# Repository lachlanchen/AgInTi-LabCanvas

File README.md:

[English](README.md) · [العربية](i18n/README.ar.md) · [Español](i18n/README.es.md) · [Français](i18n/README.fr.md) · [日本語](i18n/README.ja.md) · [한국어](i18n/README.ko.md) · [Tiếng Việt](i18n/README.vi.md) · [中文 (简体)](i18n/README.zh-Hans.md) · [中文（繁體）](i18n/README.zh-Hant.md) · [Deutsch](i18n/README.de.md) · [Русский](i18n/README.ru.md)

<p align="center">

</p>

<h1 align="center">AgInTi LabCanvas</h1>

<p align="center">
  <strong>Editable scientific figure and experiment-design studio for agent workflows.</strong><br>
  Chat, preview, decompose, route, and rebuild paper figures through Blender, OpenSCAD, BioRender, AgInTi, KiCad, Unity, Unreal, and MCP-style tool bridges.
</p>

<!-- support:start -->

<!-- support:end -->

## What It Does

AgInTi LabCanvas is a small local control plane for agent-assisted scientific visuals and app automation. It keeps generated figures editable: an overview image can start an idea, but final outputs are rebuilt from atomic parts, scene specs, CAD files, manifests, and tool-specific artifacts.

## Current Highlights

| Area | What is ready | Entry point |
| --- | --- | --- |
| Workspace agent | Persistent direct chat, dynamic low-to-xhigh model routing, durable tasks, cancellation, and artifact return across all lab tools | [docs/WORKSPACE_AGENT.md](docs/WORKSPACE_AGENT.md) |
| Web studio | Agent chat, room-based persistent sessions, artifact canvas, backend settings, multilingual UI | `labcanvas web --port 8787 --open`, `/rooms` |
| Presentations | Editable manifest-driven PPTX, selective visual assets, generated-image policy gates, and PDF/PNG preview inspection | `labcanvas presentation`, [pipeline](docs/PRESENTATION_PIPELINE.md) |
| Paper figures | Exact `NxM` SVG grids, AgInTi image dry-run payloads, editable artifact manifest | [docs/EDITABLE_FIGURE_PIPELINE.md](docs/EDITABLE_FIGURE_PIPELINE.md) |
| Grant projects | Durable Codex goal workspace, traceable evidence, editable BioRender/SVG/TeX figures, checked LaTeX/PDF, and mandatory chat delivery | `labcanvas grant init`, `labcanvas grant run`, [BioRender bridge](agentic_tools/biorender_agent/README.md) |
| Protein structures | Reused ProteinStructure AlphaFold Server pipeline, persistent logged-in CDP/noVNC browser, downloads, metrics, plots, and screenshots | `labcanvas protein start`, [handoff](references/proteinstructure-alphafold-labcanvas-handoff.md) |
| 3D setup renders | JSON scene specs to Blender PNG and `.blend` output | [docs/SCENE_SPEC.md](docs/SCENE_SPEC.md) |
| CAD devices | OpenSCAD exports and C-mount reflector adapter CAD | [cad/README.md](cad/README.md) |
| Board/CAD tasks | Shared CLI and web-chat workflow for KiCad, OpenSCAD, renders, and manufacturing prep | [docs/BOARD_CAD_TASKS.md](docs/BOARD_CAD_TASKS.md) |
| PCB manufacturing | KiCad HYBEC and Lumileds boards, DRC/ERC, JLCPCB Gerber ZIPs | [pcb](pcb) |
| LabVIEW automation | Linux install probe, MCP candidate research, stdio-to-HTTP bridge | [agentic_tools/labview_mcp_agent](agentic_tools/labview_mcp_agent) |
| Android control | Dedicated noVNC/scrcpy desktop and ADB wrapper for the Mi MIX 2S real device plus matching AVD profile | [docs/ANDROID_DEVICE_CONTROL.md](docs/ANDROID_DEVICE_CONTROL.md) |
| WeChat chatops | Isolated Linux GUI, direct local message mirror, exact-token per-chat media isolation, save-only default for unaccompanied videos, serialized text/file delivery, bounded no-backlog recovery, and CAD/PCB/Blender artifact return | [docs/WECHAT_AUTOMATION.md](docs/WECHAT_AUTOMATION.md), [full control manual](agentic_tools/wechat_gui_agent/docs/FULL_CONTROL_MANUAL.md), [robust operations](agentic_tools/wechat_gui_agent/docs/ROBUST_EFFICIENT_OPERATIONS.md) |
| WeCom bridge | Official AI Bot and `wecom-cli` transports plus allowlisted GUI/Android relays, exact voice/media transcription, content-idempotent file sends, per-chat sessions, member archives, immediate `#daily` research, and LaTeX report recovery | [setup and architecture](docs/WECOM_API_BRIDGE.md), [stable GUI interface](agentic_tools/wecom_agent/docs/GUI_RELAY_INTERFACE.md) |
| LALACHAN video handoff | Story drafting, Xiaoyunque browser generation, MP4 download, repo/Nutstore copy, and LazyEdit permission gates for WeChat workers | [references/lalachan-story-video-handoff-for-wechat.md](references/lalachan-story-video-handoff-for-wechat.md) |
| Video publish handoff | Agents resolve exact videos and context, then delegate subtitle correction, metadata, logo/subtitle burn, packaging, and public posting to LazyEdit/AutoPublish | [references/lazyedit-agent-integration-handoff.md](references/lazyedit-agent-integration-handoff.md) |
| Social content agent | Persistent Codex campaigns, source-grounded platform drafts, SQLite history, Postiz/X MCP adapters, and exact-content publication approvals | [agentic_tools/social_content_agent](agentic_tools/social_content_agent) |
| App routing | Blender, BioRender, Unity, Unreal, and custom target dispatch | [docs/RESEARCH.md](docs/RESEARCH.md) |

## Quick Start

### Model Policy

Automatic LabCanvas turns use the shared [`configs/model-policy.json`](configs/model-policy.json):
AgInTiFlow is the primary persistent backend, with DeepSeek first and LocalLLM
as a same-session provider handoff. Established LabCanvas and sibling-project
routines remain the execution layer. Codex (`auto-code-review` or
`gpt-5.6-sol`) and Claude Code remain explicit opt-in compatibility backends;
explicit backend, model, and effort selections still win. See the
[AgInTi primary-agent handoff](references/aginti-primary-labcanvas-agent-handoff-2026-08-18.md)
for goal, context, artifact, fallback, and acceptance contracts.

Run from a source checkout:

```bash
PYTHONPATH=src python -m agenticapp list
PYTHONPATH=src python -m agenticapp doctor
PYTHONPATH=src python -m agenticapp web --port 8787 --open
PYTHONPATH=src python -m agenticapp agent capabilities
PYTHONPATH=src python -m agenticapp agent chat "Design and render a C-mount sensor holder"
PYTHONPATH=src python -m agenticapp grant run "Draft specific aims with verified evidence and an editable figure" --title "Research Grant" --dry-run
PYTHONPATH=src python -m agenticapp studio biorender-figure "Three-panel mechanism figure" --panel "A: mechanism" --panel "B: intervention" --panel "C: validation" --json
PYTHONPATH=src python -m agenticapp protein start --json
PYTHONPATH=src python -m agenticapp protein status --json
PYTHONPATH=src python -m agenticapp protein submit references/target.fasta --dry-run
PYTHONPATH=src python -m agenticapp studio figure-grid "optical device icons 2x3" --rows 2 --cols 3
PYTHONPATH=src python -m agenticapp studio lab-task "prepare Lumileds no-resistor PCB and C-mount reflector CAD"
PYTHONPATH=src python -m agenticapp wechat worker reprocess TASK_ID "recover completed report" --artifact-recovery-only --send --queue agentic_tools/wecom_agent/.private/wecom_task_queue.jsonl
PYTHONPATH=src python -m unittest discover -s tests
```

The npm package has been renamed in this repository to `@lazyingart/labcanvas`, with `labcanvas` as the primary CLI and `app-auto-action` / `agenticapp` kept as compatibility aliases. The new npm package still needs a fresh authenticated publish; until then, use the source checkout or the previously published package name.

`/rooms` provides persistent LabCanvas conversations backed by the same
workspace agent as the main Studio. The local owner can use the full normal
tool set. An invited participant is restricted to plan-only turns. In the
allowlisted WeCom `LabAgent` group, trusted members can request research,
editable figures, CAD/STEP/STL, PCB/KiCad/Gerber work, OpenSCAD, and Blender
renders; generated source and preview artifacts are returned to that exact
group. Public video publication is intentionally not available there.

```bash
# After the renamed npm package is published:
npm install -g @lazyingart/labcanvas
labcanvas --version
labcanvas webapp start --port 19473
```

## Studio Workflow

1. Start with chat or a saved JSON scene spec.
2. Generate overview concepts through AgInTi image payloads or another image backend.
3. Split the figure into editable atoms: panels, icons, labels, CAD parts, renders, and TeX assembly layers.
4. Use BioRender for academic assets, OpenSCAD for mechanical layout, Blender for 3D setup renders, and KiCad for PCB artifacts.
5. Keep every artifact in the canvas manifest so later chat edits can target one part instead of flattening the whole figure.

For visible end-to-end Studio control, start the isolated LabCanvas browser and use the reusable chat controller:

```bash
scripts/launch_labcanvas_studio_novnc.sh start
scripts/labcanvas_studio_browser.py chat --message "Design and validate a C-mount holder" --effort medium
```

This submits through the real composer, monitors the exact durable task, and saves browser evidence without sharing the WeChat or Xiaoyunque profiles. See [LabCanvas Studio Browser Control](references/labcanvas-studio-browser-control.md).

## Example Commands

```bash
labcanvas scene-template experiment-setup --output my-setup.scene.json
labcanvas agent chat "Create a clean Shapr3D-compatible optical holder" --model gpt-5.6-sol --effort medium
labcanvas agent chat "Inspect the current KiCad board and report problems" --mode plan
labcanvas agent tasks
labcanvas grant init "Draft a proposal grounded in the supplied call and primary literature" --title "Research Grant"
labcanvas grant run "Complete the proposal, editable figure, and checked PDF" --project-dir output/grants/PROJECT --effort medium
labcanvas grant validate --project-dir output/grants/PROJECT --json
labcanvas presentation init "Research roadmap" --objective "Explain the evidence and next experiment" --output-dir output/presentations/roadmap
labcanvas presentation build output/presentations/roadmap/presentation.json --render --json
labcanvas presentation validate output/presentations/roadmap/presentation.json --json
labcanvas render-scene my-setup.scene.json --dry-run
labcanvas render-scene my-setup.scene.json --output-dir output/scenes
labcanvas studio openscad examples/paper-optics-setup.scene.json
labcanvas studio lab-task "prepare Lumileds no-resistor PCB and C-mount reflector CAD"
labcanvas studio lab-task "prepare Lumileds no-resistor PCB" --mode pcb --execute
labcanvas studio dispatch blender "Prepare an editable paper figure setup"
labcanvas wechat worker --chat "懒人科研" enqueue "Use AgInTi image generation to make a 2x3 microscopy icon figure"
labcanvas wechat worker --chat "懒人科研" enqueue "Use LabCanvas to render the Lumileds PCB and C-mount CAD preview"
labcanvas wechat status
labcanvas wechat hold start
labcanvas wechat stack start --web-port 19474
labcanvas wechat career-agent start --send --attach-report --organize-report --organize-chat "写作 外语 挣钱"
labcanvas wechat career-agent organize --send --organize-chat "写作 外语 挣钱" --json
labcanvas wechat audio-intake --input <exact-local-media> --output-dir output/wechat-audio-read --json
labcanvas wechat shipinhao-transcribe --source-text-file <card.txt> --output-dir output/shipinhao-read --json
PYTHONPATH=src python agentic_tools/wecom_agent/scripts/wecom_daily_research.py run --json
PYTHONPATH=src python agentic_tools/wechat_gui_agent/scripts/echomind_language_scheduler.py --daily-pdf-now
labcanvas social project add --repo ../ZhJpBook --id pocketpolyglot
labcanvas social campaign create --project pocketpolyglot --name introduction --objective "Introduce the usable open-source Studio" --platform x --platform reddit:r/languagelearning --platform hackernews
labcanvas social draft generate CAMPAIGN_ID --dry-run --json
scripts/mix2s on --serial <MIX2S_SERIAL>
scripts/mix2s status --serial <MIX2S_SERIAL>
scripts/mix2s off --serial <MIX2S_SERIAL>
agentic_tools/android_device_agent/scripts/android_control.py status --serial <MIX2S_SERIAL>
agentic_tools/biorender_agent/scripts/start_biorender_stack.sh
python agentic_tools/biorender_agent/scripts/probe_biorender_mcp.py --json
```

For a local Blender bridge test:

```bash
scripts/install_blender_portable.sh
labcanvas --config configs/blender-local-command.example.json doctor
labcanvas --config configs/blender-local-command.example.json dispatch blender "Draw a welcoming modern building with a tower"
```

## Architecture

```text
Agent / MCP client / CLI / persistent web chat
        |
        | resumed session + dynamic policy + durable task
        v
AgInTi LabCanvas
        |
        | callable routines + target registry + artifact manifest
        v
Blender · OpenSCAD · BioRender · AgInTi · KiCad · LabVIEW · Unity · Unreal
```

Every target dispatch receives a reviewable JSON envelope:

```json
{
  "target": "blender",
  "kind": "blender",
  "instruction": "Create a red cube at the origin",
  "payload": {},
  "metadata": {
    "source": "labcanvas"
  }
}
```

Copy `configs/targets.example.json` to `labcanvas.targets.json` for local ports, commands, and tokens. This override file is ignored by git.

## Validation

```bash
npm test
npm run pack:dry-run
PYTHONPATH=src python -m agenticapp doctor
```

Keep transport behavior covered by tests before adding live editor features. Review [SECURITY.md](SECURITY.md) before enabling live dispatch to editor bridges or browser sessions.

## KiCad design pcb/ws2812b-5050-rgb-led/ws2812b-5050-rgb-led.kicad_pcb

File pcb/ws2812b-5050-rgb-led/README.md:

# WS2812B 5050 RGB LED Carrier PCB

This generated KiCad project adapts the existing 24 mm round LED carrier style
to a single WS2812B 5050 addressable RGB LED.

- Board outline: 24 mm circular carrier.
- Mounting: four M2 NPTH holes on a 12 x 12 mm pattern.
- LED: WS2812B 5050 PLCC-4, centered on the board.
- Headers: two 1x02 2.54 mm side connectors. Left side is `DOUT`/`5V`;
  right side is `GND`/`DIN`.
- `DIN` is routed directly to the LED for a cleaner single-LED carrier. Add an
  external 220-470 ohm series resistor only when the controller lead is long or
  noisy.
- Top copper is intentionally simple: one visible route for each LED foot
  (`VDD`, `DOUT`, `GND`, `DIN`).
- Local supply stability: `0.1 uF` 0603 capacitor on `B.Cu`; it connects from
  the back side through the side header pads so it does not appear as another
  LED leg on the top render.

## Datasheet Notes

The WS2812B datasheet identifies the package as a 5050 integrated RGB LED and
controller. The pinout used here is:

1. `VDD`
2. `DOUT`
3. `VSS`
4. `DIN`

Run it from a nominal 5 V supply. If the controller is 3.3 V logic while the LED
is powered at 5 V, use a level shifter or verify that the DIN high level still
meets the datasheet threshold.

## Files

- `ws2812b-5050-rgb-led.kicad_pcb`: generated KiCad PCB.
- `ws2812b-5050-rgb-led-dataset.json`: source assumptions and dimensions.
- `references/`: downloaded datasheet copies when available.
- `artifacts/ws2812b-5050-rgb-led-render.png`: close KiCad render.
- `artifacts/ws2812b-5050-rgb-led-render-full.png`: full-board render.
- `artifacts/ws2812b-5050-rgb-led-plain-top.png`: flat top copper and
  silkscreen plot without 3D component bodies.
- `artifacts/ws2812b-5050-rgb-led.step`: KiCad STEP export.
- `gerber/`: Gerber and Excellon drill outputs.
- `jlcpcb_order/`: optional JLC bare-board order package.

## Reproduce

```bash
python3 pcb/scripts/generate_ws2812b_5050_rgb_board.py
kicad-cli sch erc --format json --severity-all -o pcb/ws2812b-5050-rgb-led/artifacts/erc.json pcb/ws2812b-5050-rgb-led/ws2812b-5050-rgb-led.kicad_sch
kicad-cli pcb drc --format json --severity-all -o pcb/ws2812b-5050-rgb-led/artifacts/drc.json pcb/ws2812b-5050-rgb-led/ws2812b-5050-rgb-led.kicad_pcb
kicad-cli pcb export gerbers --layers F.Cu,B.Cu,F.SilkS,B.SilkS,F.Mask,B.Mask,Edge.Cuts,F.Fab,B.Fab --precision 6 -o pcb/ws2812b-5050-rgb-led/gerber pcb/ws2812b-5050-rgb-led/ws2812b-5050-rgb-led.kicad_pcb
kicad-cli pcb export drill --generate-map --map-format svg --generate-report --report-path pcb/ws2812b-5050-rgb-led/artifacts/drill-report.txt -o pcb/ws2812b-5050-rgb-led/gerber pcb/ws2812b-5050-rgb-led/ws2812b-5050-rgb-led.kicad_pcb
```

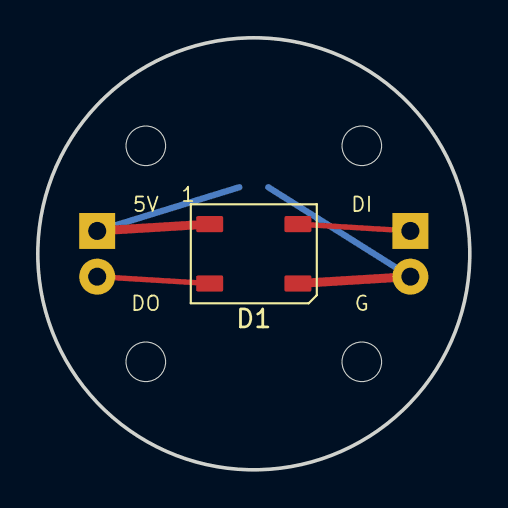
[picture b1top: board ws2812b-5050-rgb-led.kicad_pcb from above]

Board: 2 copper layers, 24.0 x 24.0 mm, 8 parts (1 on the bottom side), 4 nets.

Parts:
C1: 0.1uF; C_0603
D1: WS2812B_5050; WS2812B_5050_PLCC4
H1, H2, H3, H4: MountingHole; MountingHole_2.2mm_M2
J1: 5V_DOUT; PinHeader_1x02_P2.54mm_Vertical
J2: DIN_GND; PinHeader_1x02_P2.54mm_Vertical

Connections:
+5V: C1.1, D1.1 (VDD), J1.1 (5V)
DIN: D1.4 (DIN), J2.1 (DIN)
DOUT: D1.2 (DOUT), J1.2 (DOUT)
GND: C1.2, D1.3 (VSS), J2.2 (GND)

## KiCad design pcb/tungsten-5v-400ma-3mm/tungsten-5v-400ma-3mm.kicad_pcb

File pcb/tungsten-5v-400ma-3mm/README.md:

# 3 mm 5 V 400 mA Tungsten Lamp Carrier PCB

This generated KiCad project adapts the existing 24 mm round LED/lamp carrier
style to a very small non-polar tungsten filament lamp:

- Lamp listing: `2 W, 5 V, 400 mA, non-polar, 3 mm bulb, warm yellow`.
- Lead diameter: `0.25 mm`.
- Lead pitch: `1.00 mm`.
- PCB lamp holes: `0.45 mm` plated through holes on `1.00 mm` pitch.
- Lamp pads: `0.75 mm` diameter, leaving about `0.25 mm` copper-to-copper gap.
- Power path: short direct traces from the 1x02 input header, no resistor.
- Board outline: 24 mm circular carrier with four M2 mounting holes.

The drill is intentionally larger than the 0.25 mm foot so it is easier for JLC
to fabricate and easier to solder by hand. Verify fit with the actual lamp
before ordering a large quantity.

## Files

- `tungsten-5v-400ma-3mm.kicad_pcb`: generated KiCad PCB.
- `japan-tungsten-5v-400ma-3mm-lamp-dataset.json`: source assumptions and dimensions.
- `3dmodels/Japan_Tungsten_3mm_5V_400mA.step`: simple inspection proxy for the lamp.
- `artifacts/tungsten-5v-400ma-3mm-render.png`: close KiCad render.
- `artifacts/tungsten-5v-400ma-3mm-render-full.png`: full-board render.
- `artifacts/tungsten-5v-400ma-3mm.step`: KiCad STEP export.
- `gerber/`: Gerber and Excellon drill outputs.
- `jlcpcb_order/`: JLC China order package and settings.

## Thermal And Electrical Notes

- A 2 W tungsten bulb can still heat the PCB and nearby printed holder.
- Use direct 5 V supply. Do not add a series resistor unless the lamp sample
  behaves differently from the listing.
- Because the lamp is non-polar, the two lamp pads are named A/B only for routing.
- Keep the lamp body lifted above FR4 if the real sample radiates too much heat.

## Reproduce

```bash
python3 pcb/scripts/generate_tungsten_5v_400ma_board.py
kicad-cli sch erc --format json --severity-all -o pcb/tungsten-5v-400ma-3mm/artifacts/erc.json pcb/tungsten-5v-400ma-3mm/tungsten-5v-400ma-3mm.kicad_sch
kicad-cli pcb drc --format json --severity-all -o pcb/tungsten-5v-400ma-3mm/artifacts/drc.json pcb/tungsten-5v-400ma-3mm/tungsten-5v-400ma-3mm.kicad_pcb
kicad-cli pcb export gerbers --layers F.Cu,B.Cu,F.SilkS,B.SilkS,F.Mask,B.Mask,Edge.Cuts,F.Fab,B.Fab --precision 6 -o pcb/tungsten-5v-400ma-3mm/gerber pcb/tungsten-5v-400ma-3mm/tungsten-5v-400ma-3mm.kicad_pcb
kicad-cli pcb export drill --generate-map --map-format svg --generate-report --report-path pcb/tungsten-5v-400ma-3mm/artifacts/drill-report.txt -o pcb/tungsten-5v-400ma-3mm/gerber pcb/tungsten-5v-400ma-3mm/tungsten-5v-400ma-3mm.kicad_pcb
```

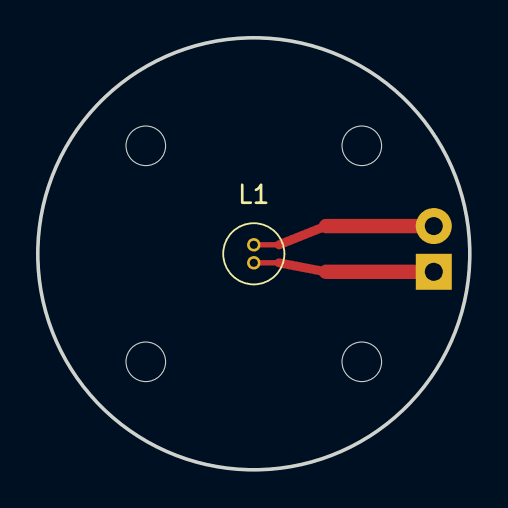
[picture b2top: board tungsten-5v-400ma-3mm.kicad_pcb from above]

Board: 2 copper layers, 24.0 x 24.0 mm, 6 parts (1 on the bottom side), 2 nets.

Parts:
H1, H2, H3, H4: MountingHole; MountingHole_2.2mm_M2
J1: 5V_IN; PinHeader_1x02_P2.54mm_Horizontal
L1: 3mm_5V_400mA_Tungsten; Japan_Tungsten_3mm_5V_400mA_1mmPitch

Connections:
LAMP_A_5V: J1.2 (A), L1.1 (A)
LAMP_B_RETURN: J1.1 (B), L1.2 (B)

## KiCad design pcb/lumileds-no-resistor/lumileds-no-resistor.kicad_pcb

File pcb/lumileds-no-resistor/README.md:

# Lumileds No-Resistor PCB

Sibling board to `pcb/hybec-hbl-273-g4`, derived from the historical Lumileds reference board at
`pcb/nhi-pcb/nhi-pcb/leds/lumileds`.

This version keeps the same 24 mm circular outline, four M2 mounting holes, `LXCL_MN08_4000`
Lumileds footprint, and horizontal 1x2 power header. The original `R1` 1.8 ohm 0201 series
resistor is removed; `J1 Pin_2` routes directly to `U1 VCC`.

## Files

- `lumileds-no-resistor.kicad_pcb` - KiCad board.
- `lumileds-no-resistor.kicad_sch` - matching schematic with no resistor symbol.
- `lumileds-no-resistor.csv` - BOM without `R1`.
- `generate_lumileds_no_resistor_board.py` - deterministic generator from the reference design.
- `fp-lib-table`, `sym-lib-table`, `footprints.pretty/`, `symbols.kicad_sym` - local library bindings.
- `artifacts/` - ERC/DRC reports, STEP export, and rendered previews.
- `gerber/` - Gerber and drill files for fabrication review.
- `jlcpcb_order/` - JLCPCB ZIP, manifest, board-order config, and order notes.
- `GENERATION_AND_ORDER_LOG.md` - detailed generation, validation, and JLC automation log.

## Validation Status

- KiCad CLI 10.0.3.
- ERC: 0 violations.
- DRC: 0 unconnected items; 5 warnings remain from copied reference geometry (`lib_footprint_mismatch` x2 and connector silkscreen clipped by the circular board edge x3).
- STEP export uses the installed KiCad 10 pin-header model at `/usr/share/kicad/3dmodels/...Horizontal.step`.

## Validate

```bash
kicad-cli sch erc --format json --severity-all -o artifacts/erc.json lumileds-no-resistor.kicad_sch
kicad-cli pcb drc --format json --severity-all -o artifacts/drc.json lumileds-no-resistor.kicad_pcb
kicad-cli pcb export step --force --include-pads --include-tracks --include-silkscreen --include-soldermask -o artifacts/lumileds-no-resistor.step lumileds-no-resistor.kicad_pcb
kicad-cli pcb export gerbers --layers F.Cu,B.Cu,F.SilkS,B.SilkS,F.Mask,B.Mask,Edge.Cuts,F.Fab,B.Fab --precision 6 -o gerber lumileds-no-resistor.kicad_pcb
kicad-cli pcb export drill --generate-map --map-format svg --generate-report --report-path artifacts/drill-report.txt -o gerber lumileds-no-resistor.kicad_pcb
xvfb-run -a kicad-cli pcb render --output artifacts/lumileds-no-resistor-render-full.png --width 1400 --height 1000 --background opaque --quality high --floor --perspective --rotate 315,0,35 --zoom 0.95 lumileds-no-resistor.kicad_pcb
```

## JLCPCB

The JLC order pack is in `jlcpcb_order/`. The China web order flow submitted this
board for review on 2026-06-15; payment was not made by automation.

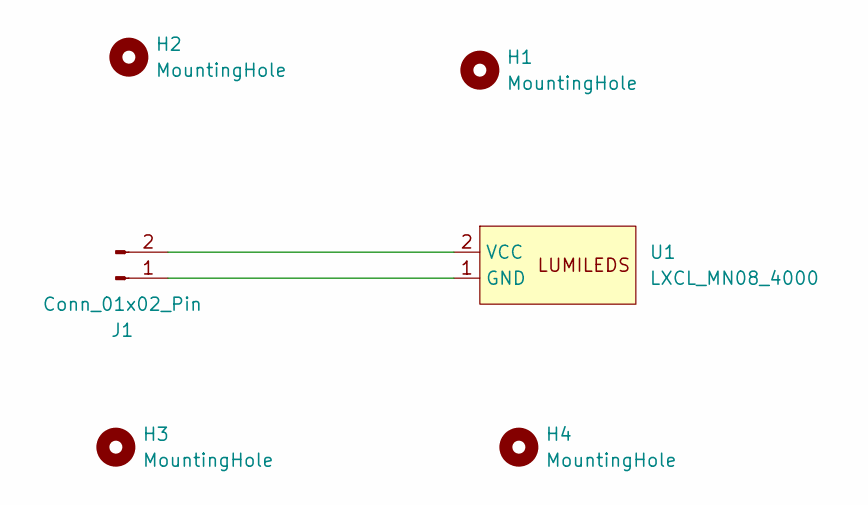
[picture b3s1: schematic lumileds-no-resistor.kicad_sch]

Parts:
H1, H2, H3, H4: MountingHole; MountingHole_2.2mm_M2
J1: Conn_01x02_Pin; PinHeader_1x02_P2.54mm_Horizontal
U1: LXCL_MN08_4000

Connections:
unnamed: J1.1, U1.1 (GND)
unnamed: J1.2, U1.2 (VCC)

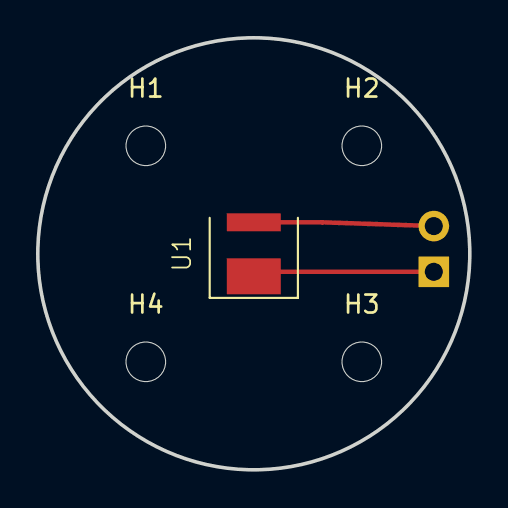
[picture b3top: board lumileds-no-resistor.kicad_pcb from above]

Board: 2 copper layers, 24.0 x 24.0 mm, 6 parts (1 on the bottom side), 2 nets.
